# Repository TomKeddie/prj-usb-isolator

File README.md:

# prj-usb-isolator

V1 USB Isolator moved from [vhs-pcbs](https://github.com/TomKeddie/vhs-pcbs/tree/master/usb-isolator)

V2 USB Isolator in smaller form factor with micro usb and disconnector button/input

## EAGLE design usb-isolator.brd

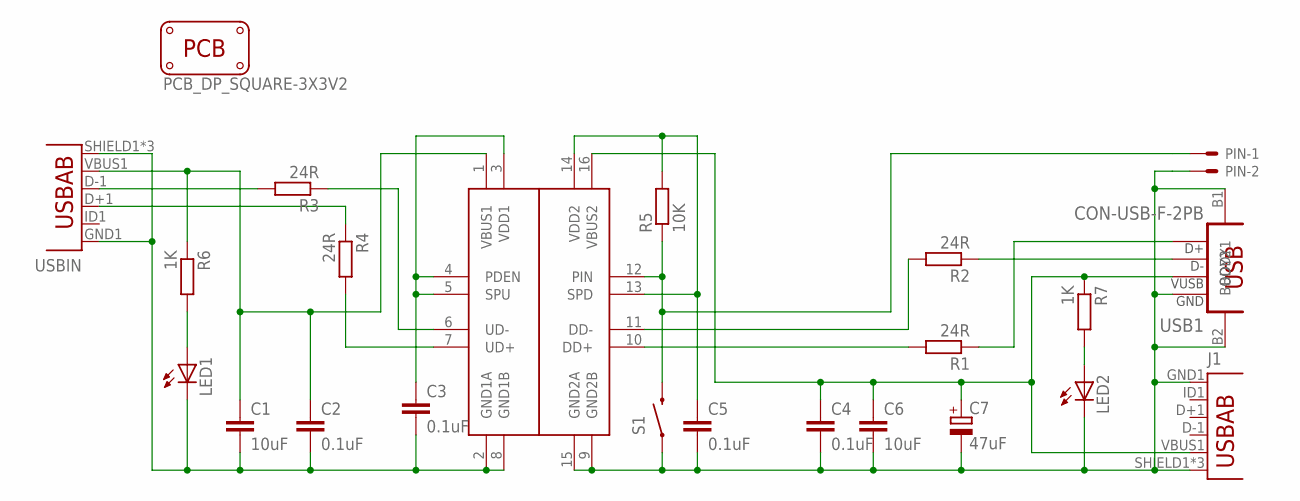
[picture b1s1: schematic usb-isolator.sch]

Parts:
C1, C6: 10uF; C0805K
C2, C3, C4, C5: 0.1uF; C0603K
C7: 47uF; D/7343-31W
IC1: ADUM3160BRWZ; SO16W
J1: USB-ABCONN-11794; USB-AB-MICRO-SMD_V03
LED1, LED2: LED-0805; LED-805
PIN: 22-23-2021
R1, R2, R3, R4: 24R; R0603
R5: 10K; R0603
R6, R7: 1K; R0603
S1: SWITCH-MOMENTARY-2SMD-1101NE; TACTILE-SWITCH-1101NE
USB1: CON-USB-F-2PB; CONN_USB_A_F
USB-ISOLATOR: PCB_DP_SQUARE-3X3V2; DP3030_V2
USBIN: USB-ABCONN-11794; USB-AB-MICRO-SMD_V03

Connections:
DD_N: R2.1, USB1.2 (D-)
DD_P: R1.1, USB1.3 (D+)
GND1: C1.2, C2.2, C3.2, IC1.2 (GND1A), IC1.8 (GND1B), LED1.C, USBIN.GND1 (GND), USBIN.SHIELD1 (SHIELD), USBIN.SHIELD2 (SHIELD), USBIN.SHIELD3 (SHIELD)
GND2: C4.2, C5.2, C6.2, C7.-, IC1.9 (GND2B), IC1.15 (GND2A), J1.GND1 (GND), J1.SHIELD1 (SHIELD), J1.SHIELD2 (SHIELD), J1.SHIELD3 (SHIELD), LED2.C, PIN.2, S1.1, USB1.4 (GND), USB1.B1 (BODY1), USB1.B2 (BODY2)
unnamed: LED1.A, R6.2
unnamed: LED2.A, R7.2
PIN: IC1.12 (PIN), PIN.1, R5.1, S1.2
R_DD_N: IC1.11 (DD-), R2.2
R_DD_P: IC1.10 (DD+), R1.2
R_UD_N: IC1.6 (UD-), R3.1
R_UD_P: IC1.7 (UD+), R4.2
UD_N: R4.1, USBIN.D+1 (D+)
UD_P: R3.2, USBIN.D-1 (D-)
VBUS1: C1.1, C2.1, IC1.1 (VBUS1), R6.1, USBIN.VBUS1 (VBUS)
VBUS2: C4.1, C6.1, C7.+, IC1.16 (VBUS2), J1.VBUS1 (VBUS), R7.1, USB1.1 (VUSB)
VDD1: C3.1, IC1.3 (VDD1), IC1.4 (PDEN), IC1.5 (SPU)
VDD2: C5.1, IC1.13 (SPD), IC1.14 (VDD2), R5.2

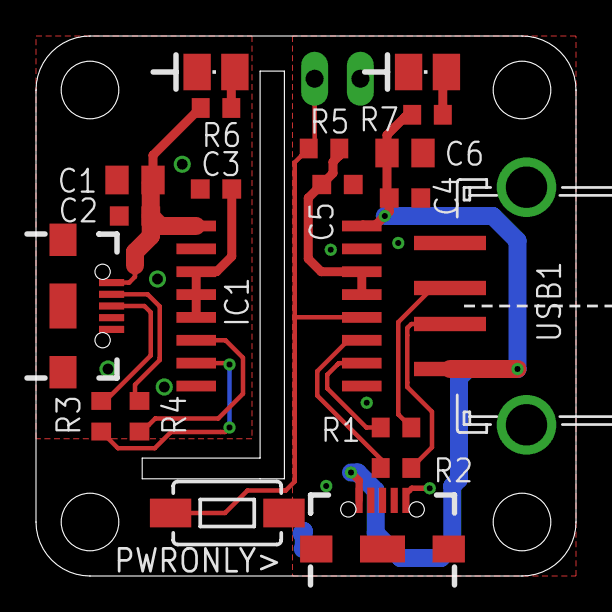
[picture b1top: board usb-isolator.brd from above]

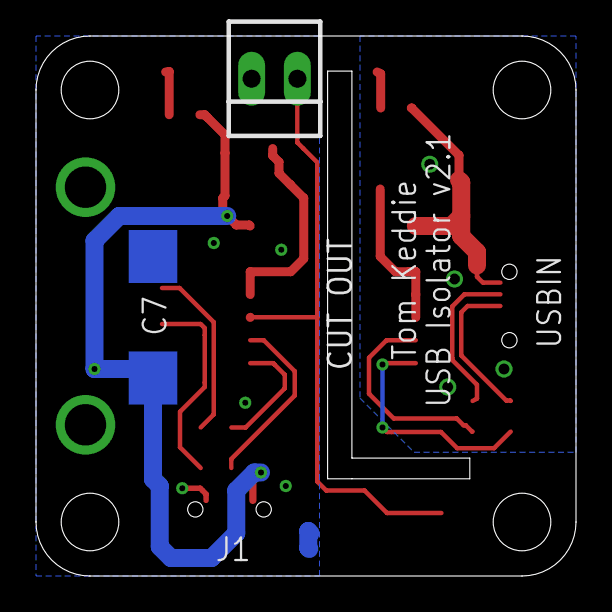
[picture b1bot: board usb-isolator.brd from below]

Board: 2 copper layers, 30.0 x 30.0 mm, 23 parts (2 on the bottom side), 17 nets.

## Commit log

2014-03-20 Added usb isolator pcb design
2014-04-01 Added BOM for usb isolator
2014-04-07 Added markdown parts list and photo
2014-04-07 Tidied parts list, added detail
2014-04-07 removed nreable html parts list
2014-04-15 Ad USB isolator workshop materials
2015-03-06 Add GTP for usb-isolator
2015-06-29 Added Digikey connector part number from Mike
2015-06-30 Added credit to Mike.
2017-03-04 Version 2.0 as submitted
2018-07-28 Updated usb isolator 2 to move button, add slot
2019-11-16 Created usb-isolator repo
2019-11-16 Removed old files, moved v1 into subdirectory
2019-11-16 Moved v2 files into new v2 directory

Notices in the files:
parts and their libraries:
SparkFun-Connectors: Licensing: Creative Commons ShareAlike 4.0 International - https://creativecommons.org/licenses/by-sa/4.0
